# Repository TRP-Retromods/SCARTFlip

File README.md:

SCARTFLip for Retrotink 5x
===========

Change the orientation of the SCART input of the Retrotink5X.

You'll need:

- PCB
- SCART Plug Male
- SCART Female Socket 180 degree 
- 2 M3x10mm screws
- 2 M2x5mm screws
- 3D Printed shell

Note: some SCART Socket varies in height and fixation, you might need to shave them a bit

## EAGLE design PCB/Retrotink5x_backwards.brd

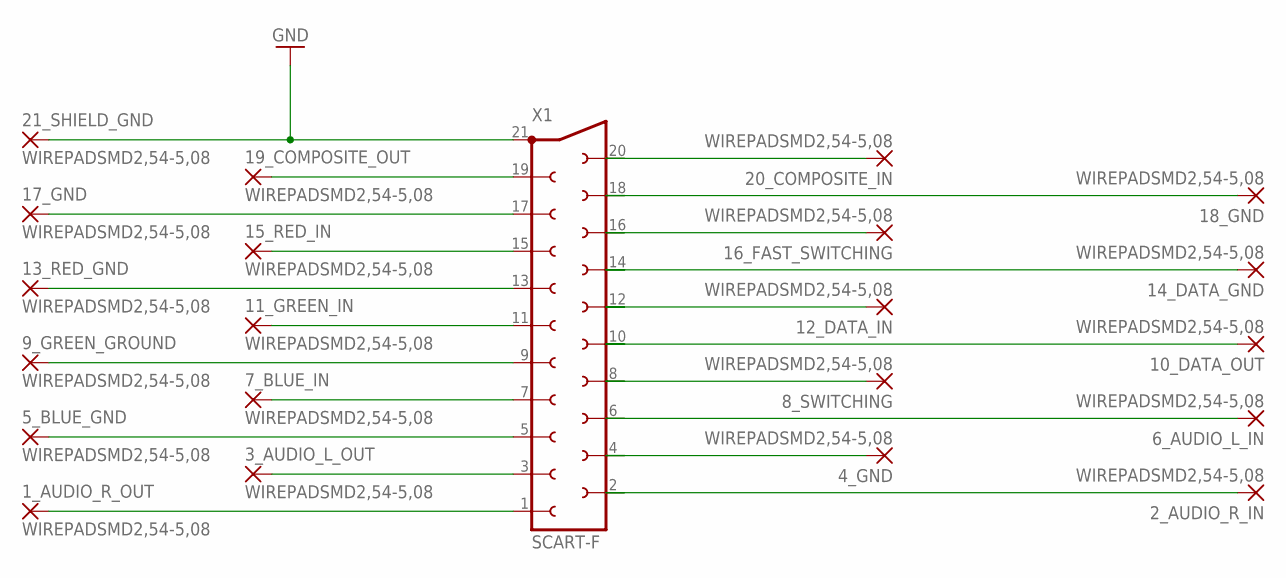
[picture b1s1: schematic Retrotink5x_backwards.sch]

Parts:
1_AUDIO_R_OUT, 2_AUDIO_R_IN, 3_AUDIO_L_OUT, 4_GND, 5_BLUE_GND, 6_AUDIO_L_IN, 7_BLUE_IN, 8_SWITCHING, 9_GREEN_GROUND, 10_DATA_OUT, 11_GREEN_IN, 12_DATA_IN, 13_RED_GND, 14_DATA_GND, 15_RED_IN, 16_FAST_SWITCHING, 17_GND, 18_GND, 19_COMPOSITE_OUT, 20_COMPOSITE_IN, 21_SHIELD_GND: WIREPADSMD2,54-5,08; SMD2,54-5,08
X1: SCART-F

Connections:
GND: 21_SHIELD_GND.1, X1.21
unnamed: 2_AUDIO_R_IN.1, X1.2
unnamed: 1_AUDIO_R_OUT.1, X1.1
unnamed: 20_COMPOSITE_IN.1, X1.20
unnamed: 4_GND.1, X1.4
unnamed: 6_AUDIO_L_IN.1, X1.6
unnamed: 19_COMPOSITE_OUT.1, X1.19
unnamed: 17_GND.1, X1.17
unnamed: 18_GND.1, X1.18
unnamed: 16_FAST_SWITCHING.1, X1.16
unnamed: 15_RED_IN.1, X1.15
unnamed: 3_AUDIO_L_OUT.1, X1.3
unnamed: 5_BLUE_GND.1, X1.5
unnamed: 7_BLUE_IN.1, X1.7
unnamed: 8_SWITCHING.1, X1.8
unnamed: 9_GREEN_GROUND.1, X1.9
unnamed: 11_GREEN_IN.1, X1.11
unnamed: 13_RED_GND.1, X1.13
unnamed: 10_DATA_OUT.1, X1.10
unnamed: 12_DATA_IN.1, X1.12
unnamed: 14_DATA_GND.1, X1.14

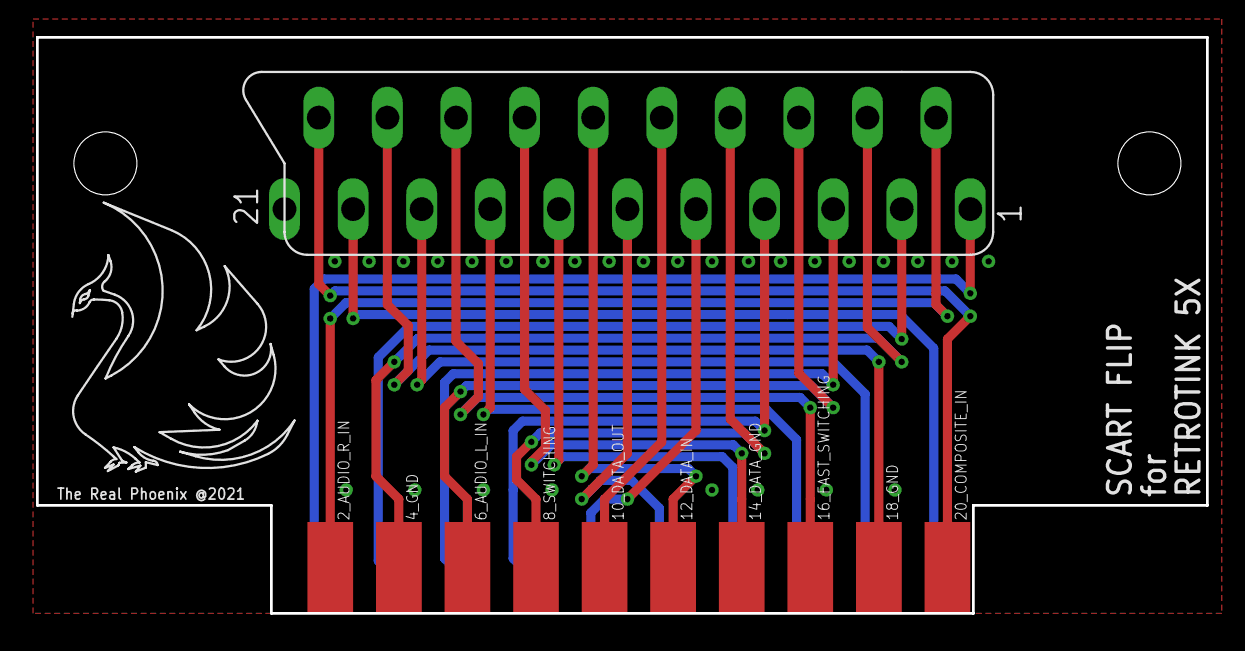
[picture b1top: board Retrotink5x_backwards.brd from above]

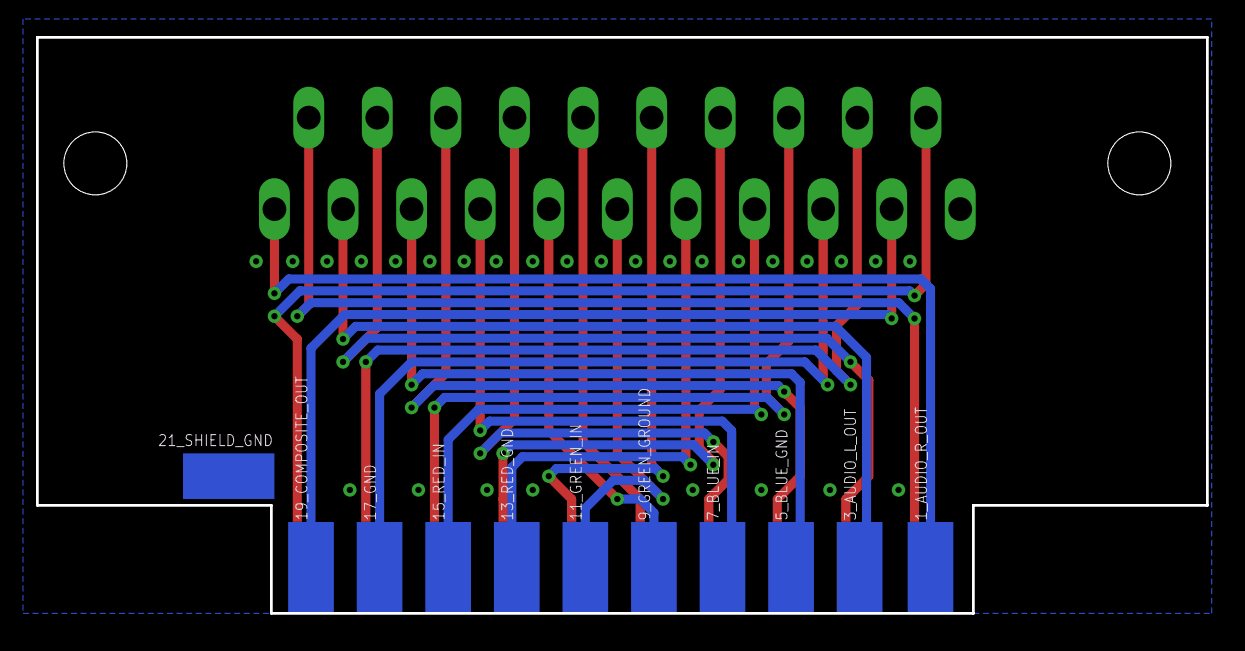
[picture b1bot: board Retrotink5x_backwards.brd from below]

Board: 2 copper layers, 65.0 x 32.0 mm, 23 parts (11 on the bottom side), 21 nets.

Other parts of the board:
U$1: LOGO

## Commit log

2022-10-02 Creation of depository
    Creation of depository
2022-10-02 Create SCARTFlip_Gerber.zip
    Add gerber files
